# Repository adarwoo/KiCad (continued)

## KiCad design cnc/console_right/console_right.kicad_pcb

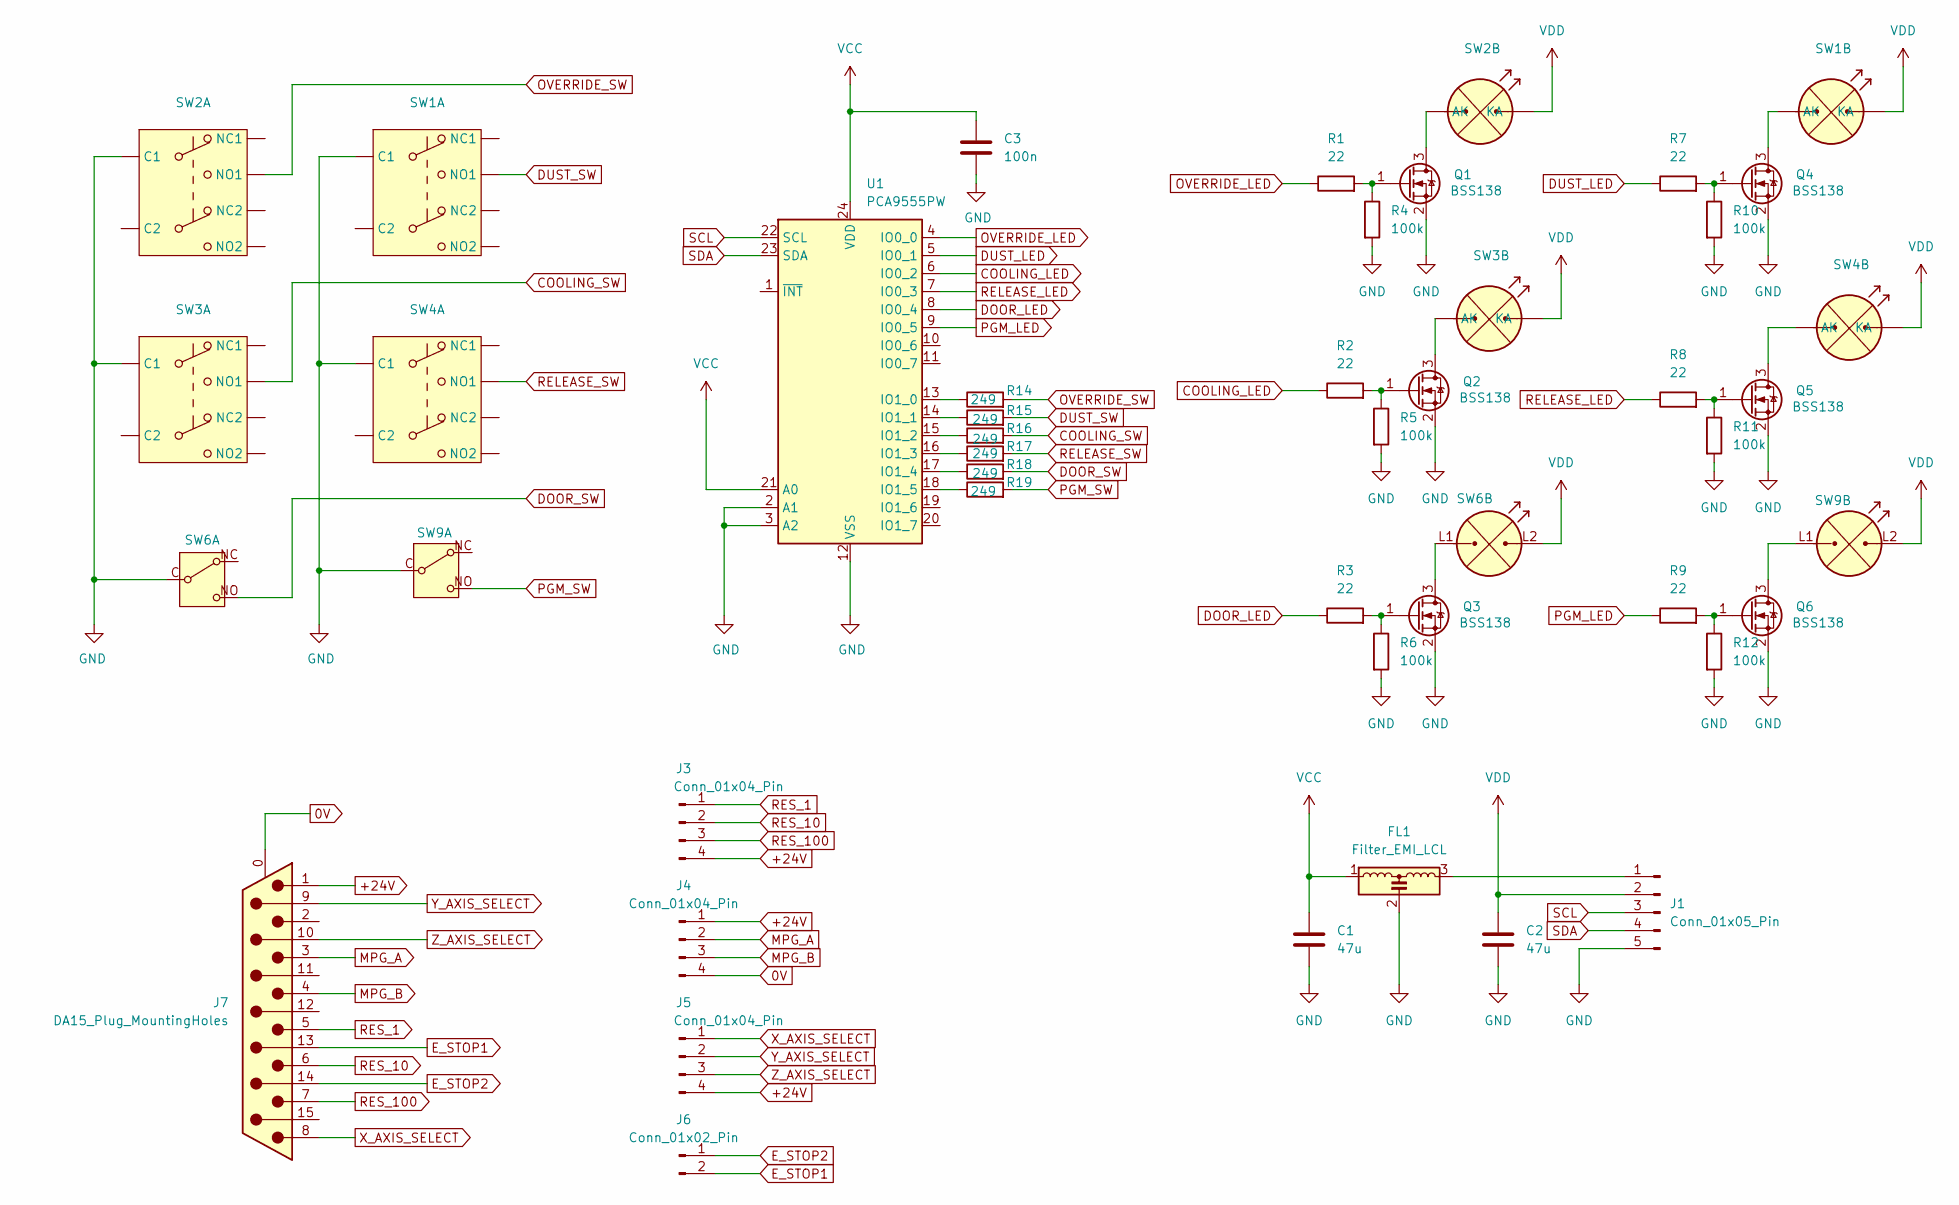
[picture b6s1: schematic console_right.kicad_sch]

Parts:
C1, C2: 47u; C_1210_3225Metric_Pad1.33x2.70mm_HandSolder
C3: 100n; C_0603_1608Metric_Pad1.08x0.95mm_HandSolder
FL1: Filter_EMI_LCL; Murata_NFM61R
J1: Conn_01x05_Pin; Molex_KK-254_AE-6410-05A_1x05_P2.54mm_Vertical
J3, J4, J5: Conn_01x04_Pin; Molex_KK-254_AE-6410-04A_1x04_P2.54mm_Vertical
J6: Conn_01x02_Pin; Molex_KK-254_AE-6410-02A_1x02_P2.54mm_Vertical
J7: DA15_Plug_MountingHoles; DSUB-15_Male_Horizontal_P2.77x2.84mm_EdgePinOffset7.70mm_Ho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
Q1, Q2, Q3, Q4, Q5, Q6: BSS138; SOT-23
R1, R2, R3, R7, R8, R9: 22; R_1206_3216Metric_Pad1.30x1.75mm_HandSolder
R4, R5, R6, R10, R11, R12: 100k; R_1206_3216Metric_Pad1.30x1.75mm_HandSolder
R14, R15, R16, R17, R18, R19: 249; R_1206_3216Metric_Pad1.30x1.75mm_HandSolder
SW1, SW2, SW3, SW4: DPDT-LED12V
SW6, SW9: PUSH_STDP_LED
U1: PCA9555PW; TSSOP-24_4.4x7.8mm_P0.65mm

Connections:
0V: J4.4, J7.0 (PAD)
+24V: J3.4, J4.1, J5.4, J7.1
COOLING_LED: R2.1, U1.6 (IO0_2)
COOLING_SW: R16.2, SW3.NO1
DOOR_LED: R3.1, U1.8 (IO0_4)
DOOR_SW: R18.2, SW6.NO
DUST_LED: R7.1, U1.5 (IO0_1)
DUST_SW: R15.2, SW1.NO1
E_STOP1: J6.2, J7.13
E_STOP2: J6.1, J7.14
GND: C1.2, C2.2, C3.2, FL1.2, J1.5, Q1.2 (S), Q2.2 (S), Q3.2 (S), Q4.2 (S), Q5.2 (S), Q6.2 (S), R4.2, R5.2, R6.2, R10.2, R11.2, R12.2, SW1.C1, SW2.C1, SW3.C1, SW4.C1, SW6.C, SW9.C, U1.2 (A1), U1.3 (A2), U1.12 (VSS)
MPG_A: J4.2, J7.3
MPG_B: J4.3, J7.4
unnamed: FL1.3, J1.1
unnamed: Q1.3 (D), SW2.L1 (AK)
unnamed: Q1.1 (G), R1.2, R4.1
unnamed: Q2.3 (D), SW3.L1 (AK)
unnamed: Q2.1 (G), R2.2, R5.1
unnamed: Q3.3 (D), SW6.L1 (AK)
unnamed: Q3.1 (G), R3.2, R6.1
unnamed: Q4.3 (D), SW1.L1 (AK)
unnamed: Q4.1 (G), R7.2, R10.1
unnamed: Q5.3 (D), SW4.L1 (AK)
unnamed: Q5.1 (G), R8.2, R11.1
unnamed: Q6.3 (D), SW9.L1 (AK)
unnamed: Q6.1 (G), R9.2, R12.1
unnamed: R14.1, U1.13 (IO1_0)
unnamed: R15.1, U1.14 (IO1_1)
unnamed: R16.1, U1.15 (IO1_2)
unnamed: R17.1, U1.16 (IO1_3)
unnamed: R18.1, U1.17 (IO1_4)
unnamed: R19.1, U1.18 (IO1_5)
OVERRIDE_LED: R1.1, U1.4 (IO0_0)
OVERRIDE_SW: R14.2, SW2.NO1
PGM_LED: R9.1, U1.9 (IO0_5)
PGM_SW: R19.2, SW9.NO
RELEASE_LED: R8.1, U1.7 (IO0_3)
RELEASE_SW: R17.2, SW4.NO1
RES_1: J3.1, J7.5
RES_10: J3.2, J7.6
RES_100: J3.3, J7.7
SCL: J1.3, U1.22 (SCL)
SDA: J1.4, U1.23 (SDA)
VCC: C1.1, C3.1, FL1.1, U1.21 (A0), U1.24 (VDD)
VDD: C2.1, J1.2, SW1.L2 (KA), SW2.L2 (KA), SW3.L2 (KA), SW4.L2 (KA), SW6.L2 (KA), SW9.L2 (KA)
X_AXIS_SELECT: J5.1, J7.8
Y_AXIS_SELECT: J5.2, J7.9
Z_AXIS_SELECT: J5.3, J7.10

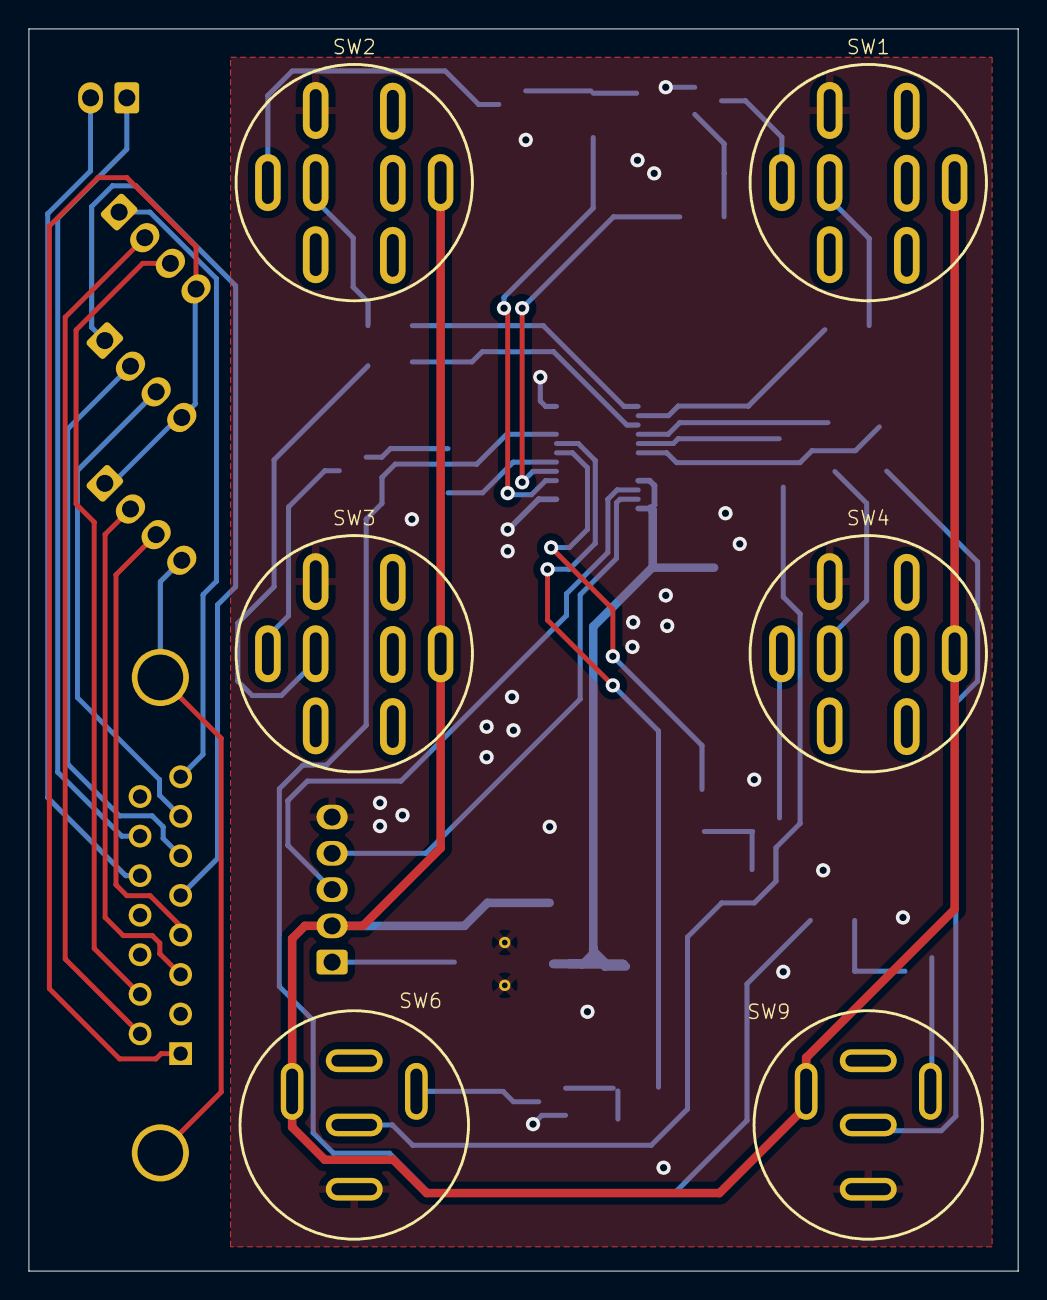
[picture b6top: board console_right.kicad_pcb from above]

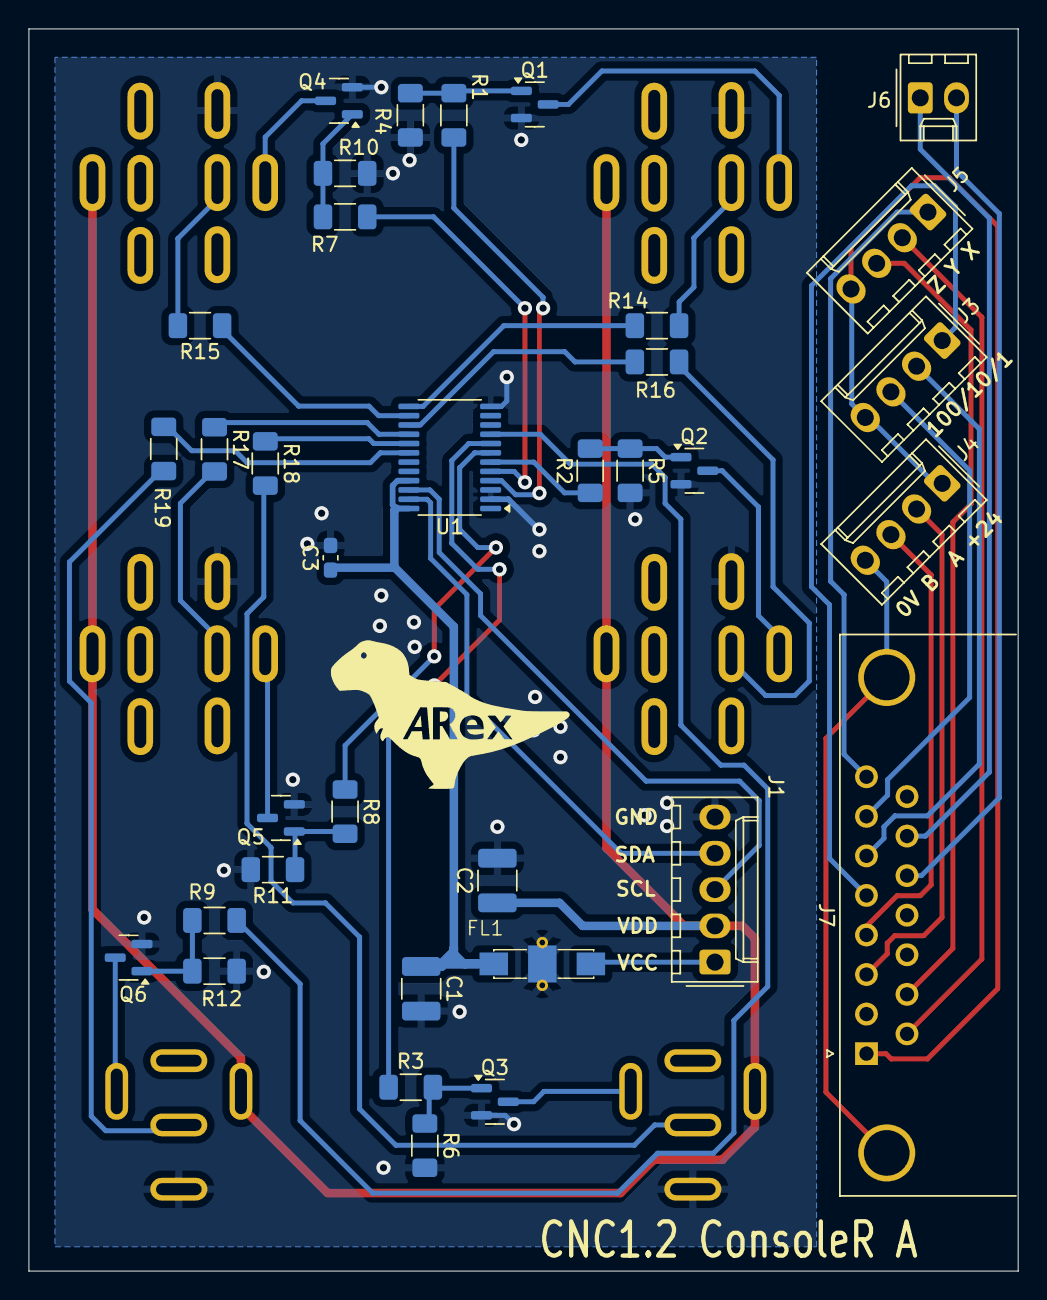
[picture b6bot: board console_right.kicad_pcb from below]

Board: 2 copper layers, 69.3 x 87.0 mm, 41 parts (35 on the bottom side), 48 nets.

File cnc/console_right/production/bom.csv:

Designator,Footprint,Quantity,Value,LCSC Part #
"C1, C2",1210,2,47u,
C3,0603,1,100n,
FL1,Murata_NFM61R,1,Filter_EMI_LCL,
J1,Molex_KK-254_AE-6410-05A_1x05_P2.54mm_Vertical,1,Conn_01x05_Pin,
"J3, J4, J5",Molex_KK-254_AE-6410-04A_1x04_P2.54mm_Vertical,3,Conn_01x04_Pin,
J6,Molex_KK-254_AE-6410-02A_1x02_P2.54mm_Vertical,1,Conn_01x02_Pin,
J7,DSUB-15_Male_Horizontal_P2.77x2.84mm_EdgePinOffset7.70mm_Housed_MountingHolesOffset9.12mm,1,DA15_Plug_MountingHoles,
"Q1, Q2, Q3, Q4, Q5, Q6",SOT-23,6,BSS138,
"R1, R2, R3, R7, R8, R9",1206,6,22,
"R10, R11, R12, R4, R5, R6",1206,6,100k,
"R14, R15, R16, R17, R18, R19",1206,6,332,
"SW1, SW2, SW3, SW4",DPDT-LED12V,4,~,
"SW6, SW9",PUSH_STDP_LED,2,~,
U1,TSSOP-24_4.4x7.8mm_P0.65mm,1,PCA9555PW,

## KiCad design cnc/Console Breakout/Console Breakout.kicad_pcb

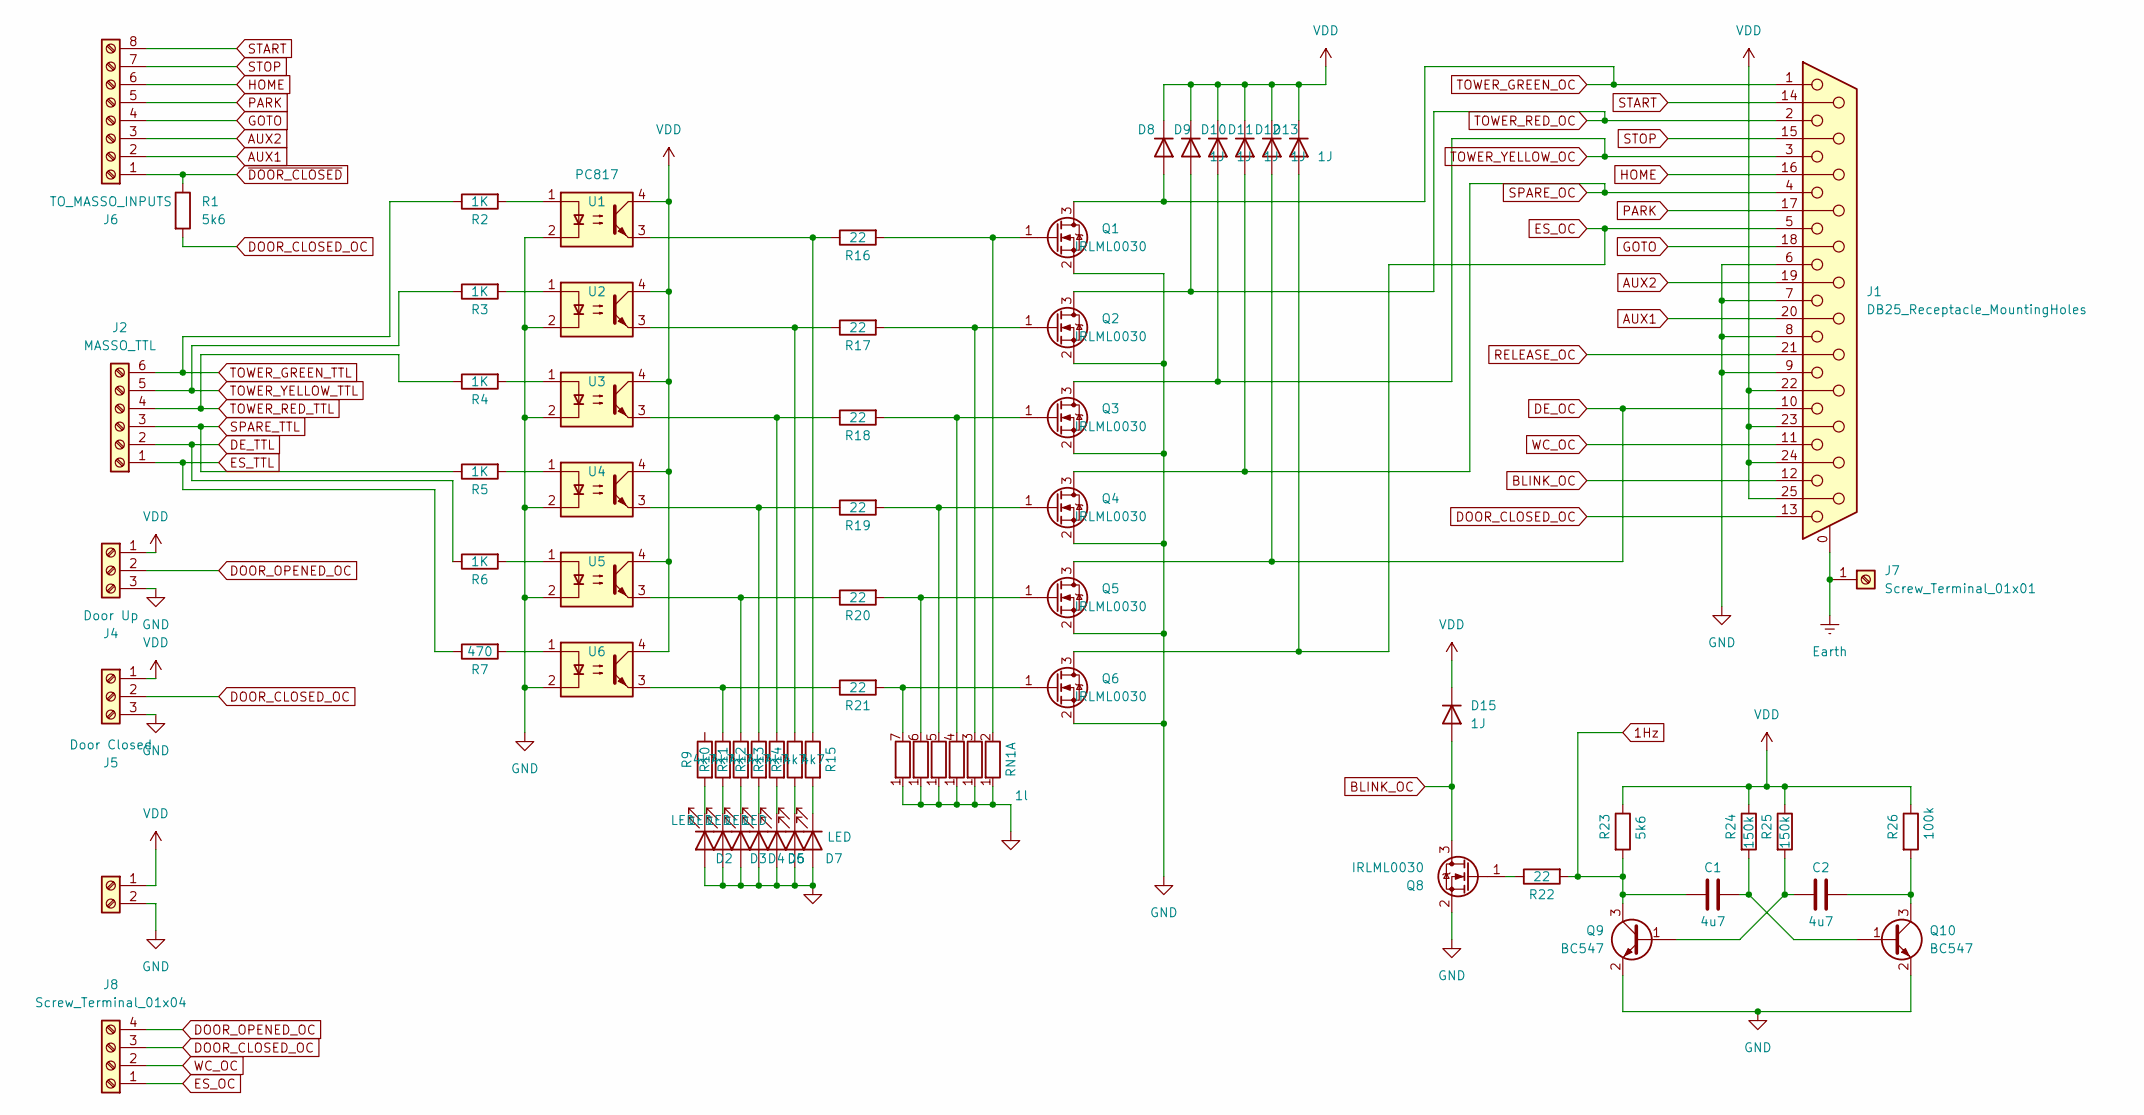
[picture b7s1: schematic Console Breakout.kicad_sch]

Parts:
C1, C2: 4u7; CP_EIA-6032-28_Kemet-C_Pad2.25x2.35mm_HandSolder
D1, D2, D3, D4, D5, D6, D7: LED; LED_D3.0mm
D8, D9, D10, D11, D12, D13: 1J; D_MicroSMP_AK
D15: 1J; D_SMA
J1: DB25_Receptacle_MountingHoles; DSUB-25_Female_Vertical_P2.77x2.84mm_MountingHoles
J2: MASSO_TTL; PhoenixContact_MCV_1,5_6-G-3.81_1x06_P3.81mm_Vertical
J3: Screw_Terminal_01x02; PhoenixContact_MCV_1,5_2-G-3.81_1x02_P3.81mm_Vertical
J4: Door Up; PhoenixContact_MCV_1,5_3-G-3.81_1x03_P3.81mm_Vertical
J5: Door Closed; PhoenixContact_MCV_1,5_3-G-3.81_1x03_P3.81mm_Vertical
J6: TO_MASSO_INPUTS; PhoenixContact_MCV_1,5_8-G-3.81_1x08_P3.81mm_Vertical
J7: Screw_Terminal_01x01; TerminalBlock_MetzConnect_360410_1x01_Horizontal_ScrewM3.0
J8: Screw_Terminal_01x04; PhoenixContact_MCV_1,5_4-G-3.81_1x04_P3.81mm_Vertical
Q1, Q2, Q3, Q4, Q5, Q6, Q8: IRLML0030; SOT-23
Q9, Q10: BC547; SOT-23
R1, R23: 5k6; R_1206_3216Metric_Pad1.30x1.75mm_HandSolder
R2, R3, R4, R5, R6: 1K; R_1206_3216Metric_Pad1.30x1.75mm_HandSolder
R7: 470; R_1206_3216Metric_Pad1.30x1.75mm_HandSolder
R9, R10, R11, R12, R13, R14, R15: 4k7; R_1206_3216Metric_Pad1.30x1.75mm_HandSolder
R16, R17, R18, R19, R20, R21, R22: 22; R_1206_3216Metric_Pad1.30x1.75mm_HandSolder
R24, R25: 150k; R_1206_3216Metric_Pad1.30x1.75mm_HandSolder
R26: 100k; R_1206_3216Metric_Pad1.30x1.75mm_HandSolder
RN1: 1l; R_Array_SIP8
U1, U2, U3, U4, U5, U6: PC817; DIP-4_W7.62mm

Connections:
1Hz: C1.1, Q9.3 (C), R22.2, R23.2
AUX1: J1.20, J6.2
AUX2: J1.19, J6.3
BLINK_OC: D15.2 (A), J1.12, Q8.3 (D)
DE_OC: D12.2 (A), J1.10, Q5.3 (D)
DE_TTL: J2.2, R6.1
DOOR_CLOSED_OC: J1.13, J5.2, J8.3, R1.2
DOOR_OPENED_OC: J4.2, J8.4
ES_OC: D13.2 (A), J1.5, J8.1, Q6.3 (D)
ES_TTL: J2.1, R7.1
Earth: J1.0 (PAD), J7.1
GND: D1.2 (A), D2.2 (A), D3.2 (A), D4.2 (A), D5.2 (A), D6.2 (A), D7.2 (A), J1.6, J1.7, J1.8, J1.9, J3.2, J4.3, J5.3, Q1.2 (S), Q2.2 (S), Q3.2 (S), Q4.2 (S), Q5.2 (S), Q6.2 (S), Q8.2 (S), Q9.2 (E), Q10.2 (E), RN1.1 (R1), U1.2, U2.2, U3.2, U4.2, U5.2, U6.2
GOTO: J1.18, J6.4
HOME: J1.16, J6.6
unnamed: D1.1 (K), R9.2
unnamed: D2.1 (K), R10.2
unnamed: D3.1 (K), R11.2
unnamed: D4.1 (K), R12.2
unnamed: D5.1 (K), R13.2
unnamed: D6.1 (K), R14.2
unnamed: D7.1 (K), R15.2
unnamed: Q1.1 (G), R16.2, RN1.2 (R1.2)
unnamed: Q2.1 (G), R17.2, RN1.3 (R2.2)
unnamed: Q3.1 (G), R18.2, RN1.4 (R3.2)
unnamed: Q4.1 (G), R19.2, RN1.5 (R4.2)
unnamed: Q5.1 (G), R20.2, RN1.6 (R5.2)
unnamed: Q6.1 (G), R21.2, RN1.7 (R6.2)
unnamed: Q8.1 (G), R22.1
unnamed: C2.1, Q9.1 (B), R25.2
unnamed: C1.2, Q10.1 (B), R24.2
unnamed: C2.2, Q10.3 (C), R26.2
unnamed: R2.2, U1.1
unnamed: R3.2, U2.1
unnamed: R4.2, U3.1
unnamed: R5.2, U4.1
unnamed: R6.2, U5.1
unnamed: R7.2, U6.1
unnamed: R10.1, R21.1, U6.3
unnamed: R11.1, R20.1, U5.3
unnamed: R12.1, R19.1, U4.3
unnamed: R13.1, R18.1, U3.3
unnamed: R14.1, R17.1, U2.3
unnamed: R15.1, R16.1, U1.3
PARK: J1.17, J6.5
RELEASE_OC: J1.21
SPARE_OC: D11.2 (A), J1.4, Q4.3 (D)
SPARE_TTL: J2.3, R5.1
START: J1.14, J6.8
STOP: J1.15, J6.7
TOWER_GREEN_OC: D8.2 (A), J1.1, Q1.3 (D)
TOWER_GREEN_TTL: J2.6, R2.1
TOWER_RED_OC: D9.2 (A), J1.2, Q2.3 (D)
TOWER_RED_TTL: J2.4, R4.1
TOWER_YELLOW_OC: D10.2 (A), J1.3, Q3.3 (D)
TOWER_YELLOW_TTL: J2.5, R3.1
VDD: D8.1 (K), D9.1 (K), D10.1 (K), D11.1 (K), D12.1 (K), D13.1 (K), D15.1 (K), J1.22, J1.23, J1.24, J1.25, J3.1, J4.1, J5.1, R23.1, R24.1, R25.1, R26.1, U1.4, U2.4, U3.4, U4.4, U5.4, U6.4
WC_OC: J1.11, J8.2
~DOOR_CLOSED: J6.1, R1.1

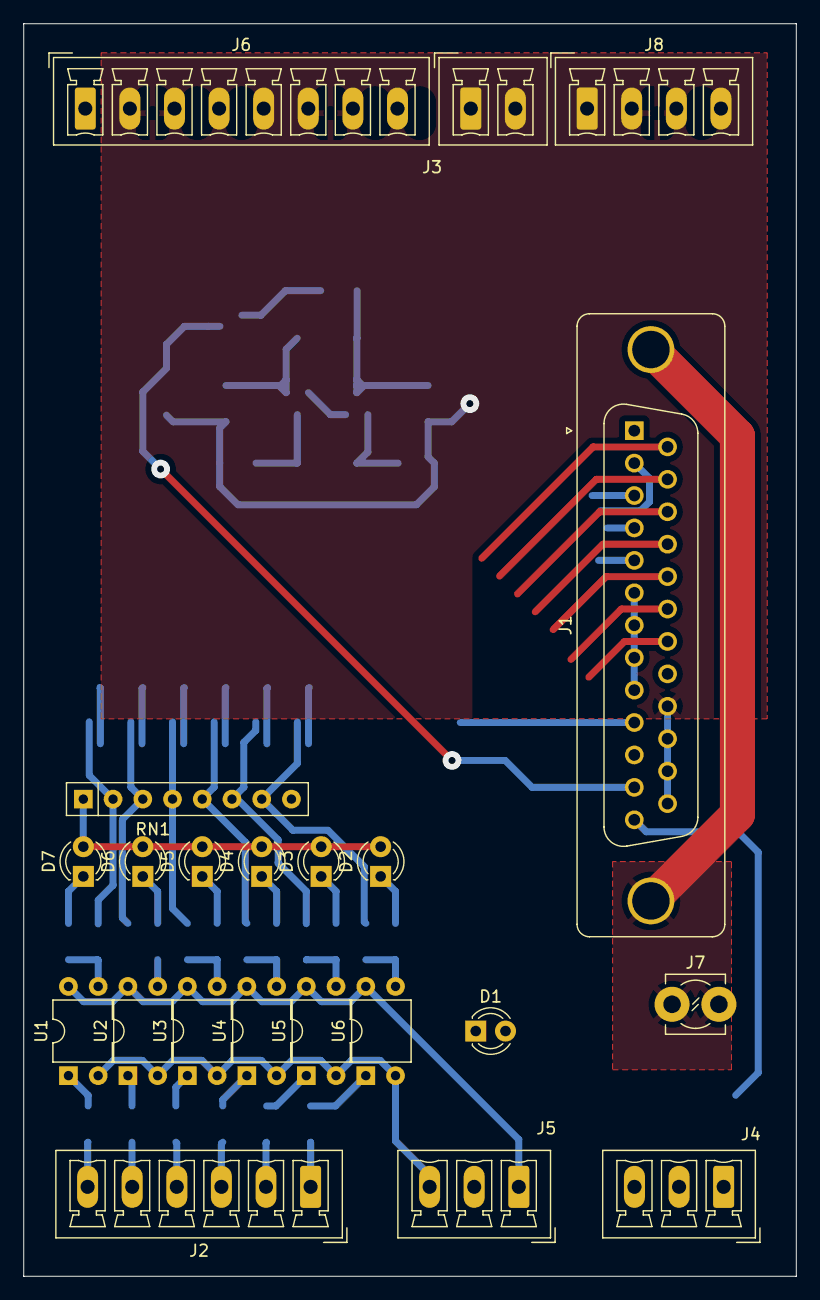
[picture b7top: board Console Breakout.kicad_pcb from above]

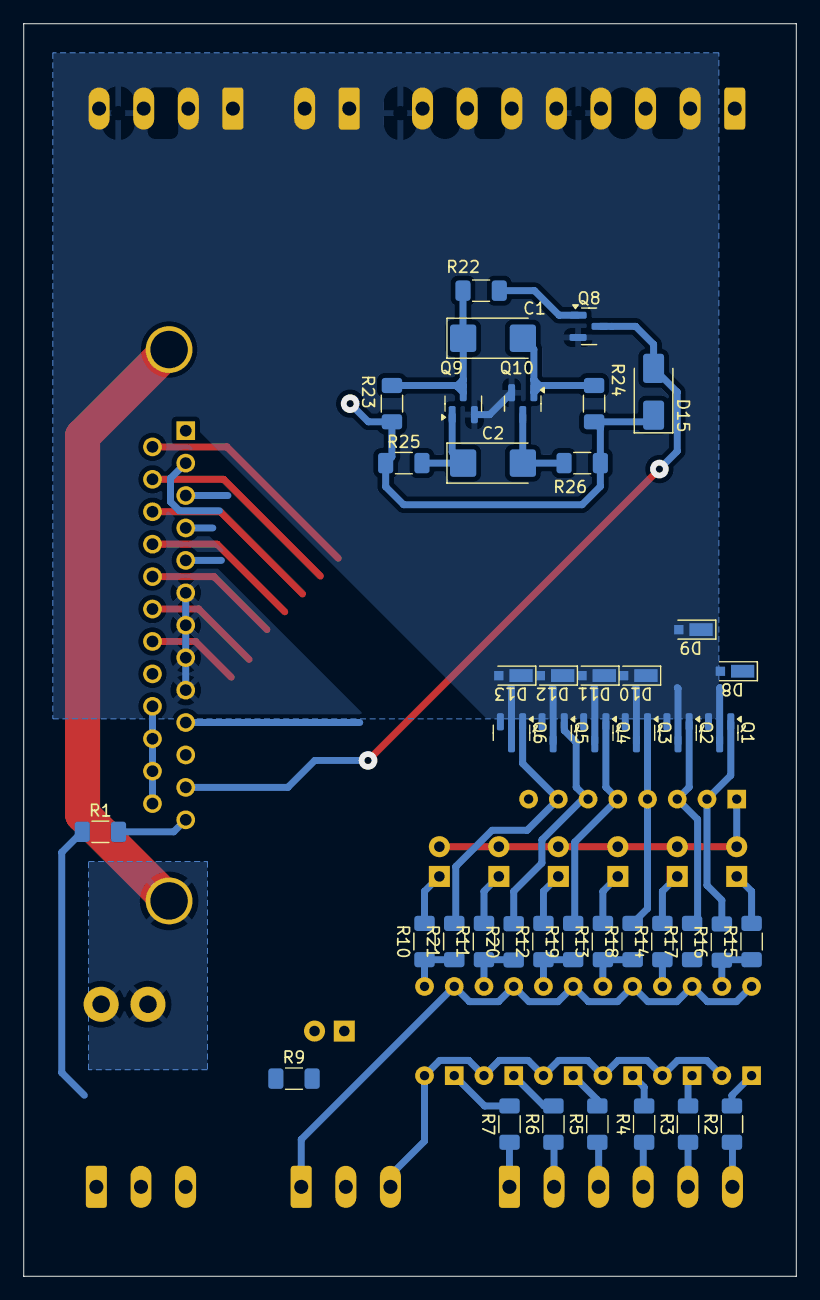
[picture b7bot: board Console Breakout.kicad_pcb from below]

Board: 2 copper layers, 66.0 x 107.0 mm, 65 parts (43 on the bottom side), 57 nets.

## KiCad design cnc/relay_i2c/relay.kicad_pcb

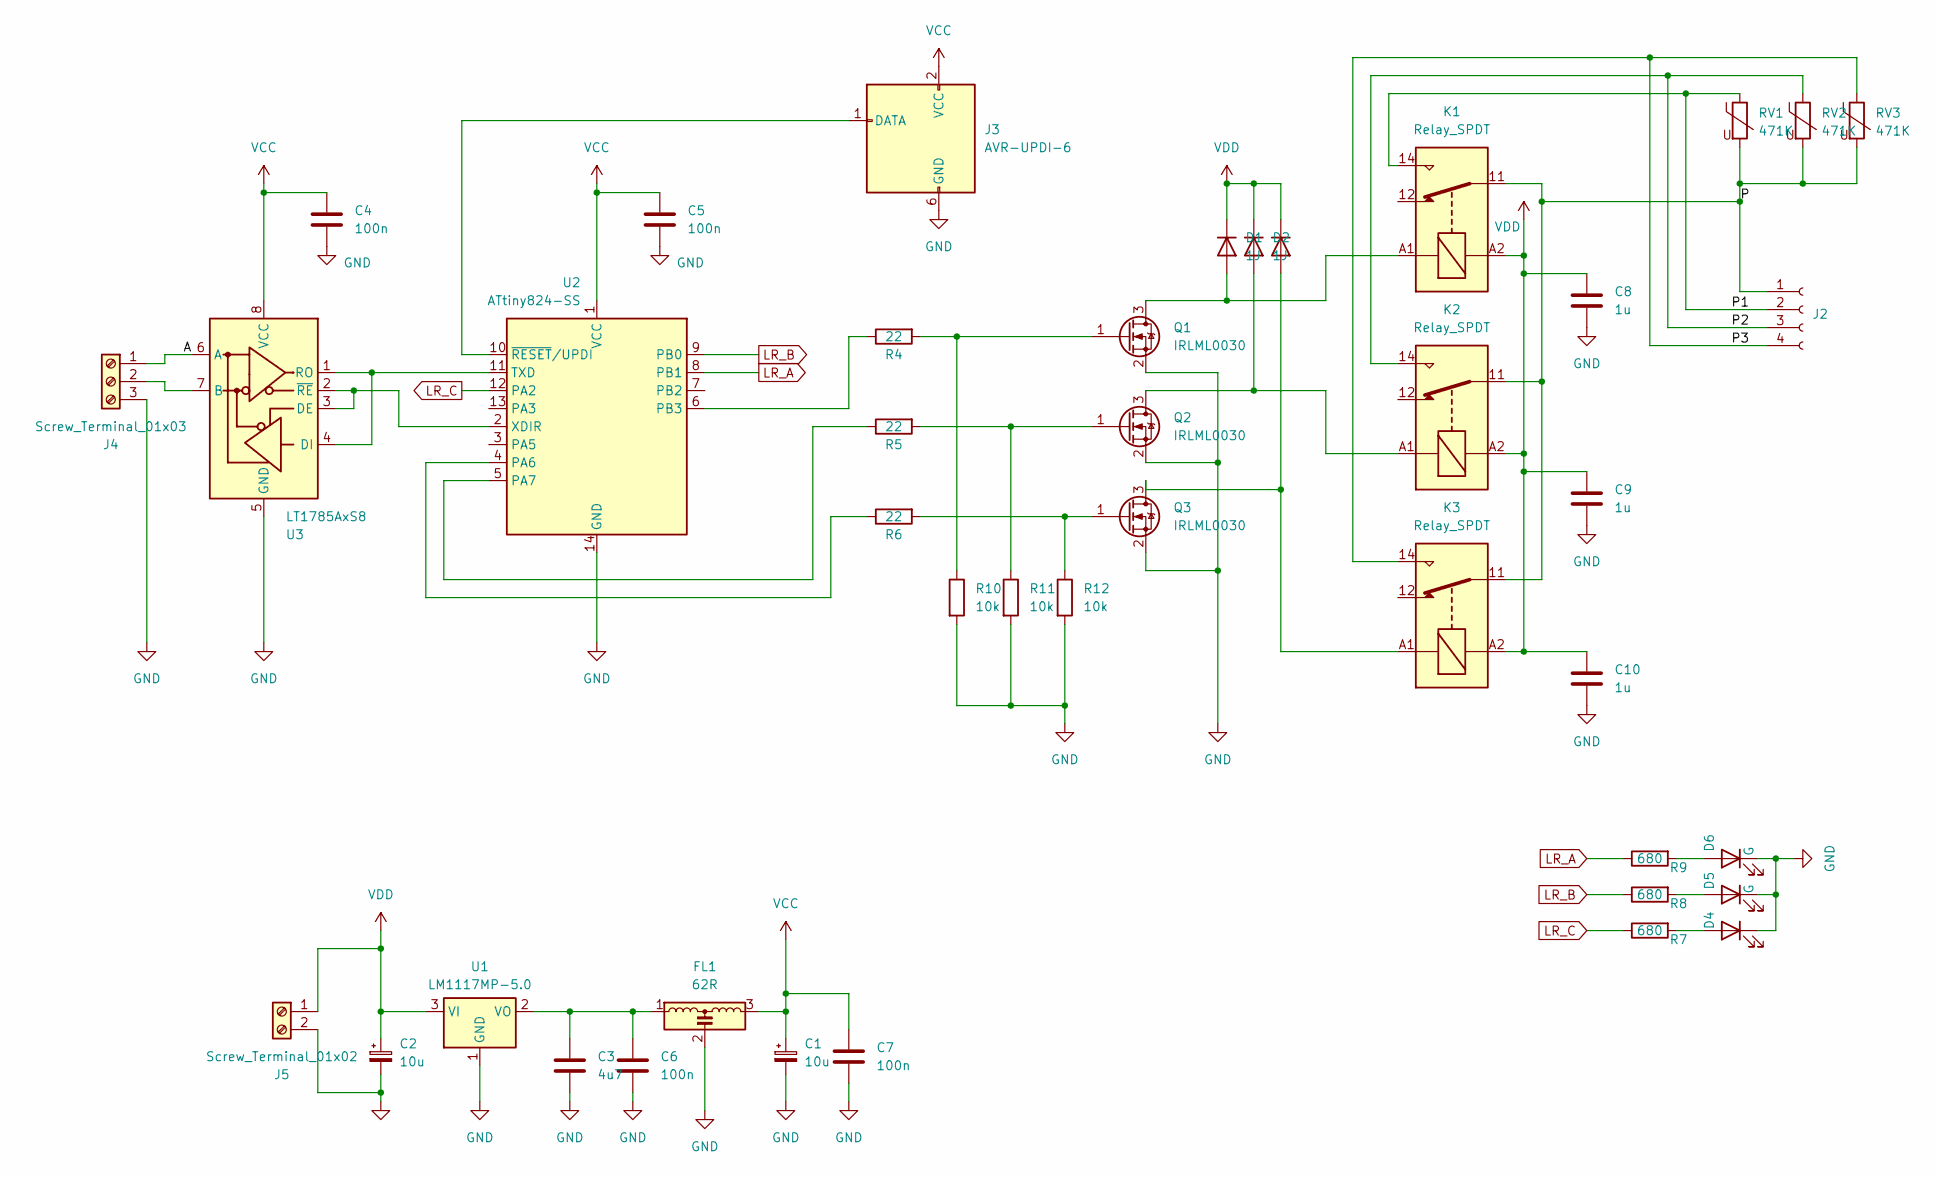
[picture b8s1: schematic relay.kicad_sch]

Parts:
C1, C2: 10u; CP_EIA-6032-28_Kemet-C
C3: 4u7; C_1206_3216Metric_Pad1.33x1.80mm_HandSolder
C4, C5, C6, C7: 100n; C_0805_2012Metric_Pad1.18x1.45mm_HandSolder
C8, C9, C10: 1u; C_1206_3216Metric_Pad1.33x1.80mm_HandSolder
D1, D2, D3: 1J; D_SMA
D4, D5, D6: G; LED_D3.0mm
FL1: 62R; Murata_NFM61R
J2: TerminalBlock_Phoenix_MKDS-1,5-4_1x04_P5.00mm_Horizontal
J3: AVR-UPDI-6; PinHeader_2x03_P2.54mm_Vertical
J4: Screw_Terminal_01x03; PhoenixContact_MCV_1,5_3-G-3.81_1x03_P3.81mm_Vertical
J5: Screw_Terminal_01x02; PhoenixContact_MCV_1,5_2-G-3.81_1x02_P3.81mm_Vertical
K1, K2, K3: Relay_SPDT; Relay_SPDT_Omron_G2RL-1-E
Q1, Q2, Q3: IRLML0030; SOT-23
R4, R5, R6: 22; R_1206_3216Metric_Pad1.30x1.75mm_HandSolder
R7, R8, R9: 680; R_1206_3216Metric_Pad1.30x1.75mm_HandSolder
R10, R11, R12: 10k; R_1206_3216Metric_Pad1.30x1.75mm_HandSolder
RV1, RV2, RV3: 471K; RV_Disc_D9mm_W3.3mm_P5mm
U1: LM1117MP-5.0; SOT-223-3_TabPin2
U2: ATtiny824-SS; SOIC-14_3.9x8.7mm_P1.27mm
U3: LT1785AxS8; SOIC-8_3.9x4.9mm_P1.27mm

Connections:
/A: J4.1, U3.6 (A)
/P: J2.1, K1.11, K2.11, K3.11, RV1.2, RV2.2, RV3.2
/P1: J2.2, K1.14, RV1.1
/P2: J2.3, K2.14, RV2.1
/P3: J2.4, K3.14, RV3.1
GND: C1.2, C2.2, C3.2, C4.2, C5.2, C6.2, C7.2, C8.2, C9.2, C10.2, D4.1 (K), D5.1 (K), D6.1 (K), FL1.2, J3.6 (GND), J4.3, J5.2, Q1.2 (S), Q2.2 (S), Q3.2 (S), R10.2, R11.2, R12.2, U1.1 (GND), U2.14 (GND), U3.5 (GND)
LR_A: R9.1, U2.8 (PB1)
LR_B: R8.1, U2.9 (PB0)
LR_C: R7.1, U2.12 (PA2)
unnamed: D1.2 (A), K1.A1, Q1.3 (D)
unnamed: D2.2 (A), K2.A1, Q2.3 (D)
unnamed: D3.2 (A), K3.A1, Q3.3 (D)
unnamed: D4.2 (A), R7.2
unnamed: D5.2 (A), R8.2
unnamed: D6.2 (A), R9.2
unnamed: J3.1 (DATA), U2.10 (~RESET/UPDI)
unnamed: J4.2, U3.7 (B)
unnamed: Q1.1 (G), R4.2, R10.1
unnamed: Q2.1 (G), R5.2, R11.1
unnamed: Q3.1 (G), R6.2, R12.1
unnamed: C3.1, C6.1, FL1.1, U1.2 (VO)
unnamed: U2.11 (TXD), U3.1 (RO), U3.4 (DI)
unnamed: U2.2 (XDIR), U3.2 (~RE), U3.3 (DE)
unnamed: R6.1, U2.4 (PA6)
unnamed: R5.1, U2.5 (PA7)
unnamed: R4.1, U2.6 (PB3)
VCC: C1.1, C4.1, C5.1, C7.1, FL1.3, J3.2 (VCC), U2.1 (VCC), U3.8 (VCC)
VDD: C2.1, C8.1, C9.1, C10.1, D1.1 (K), D2.1 (K), D3.1 (K), J5.1, K1.A2, K2.A2, K3.A2, U1.3 (VI)

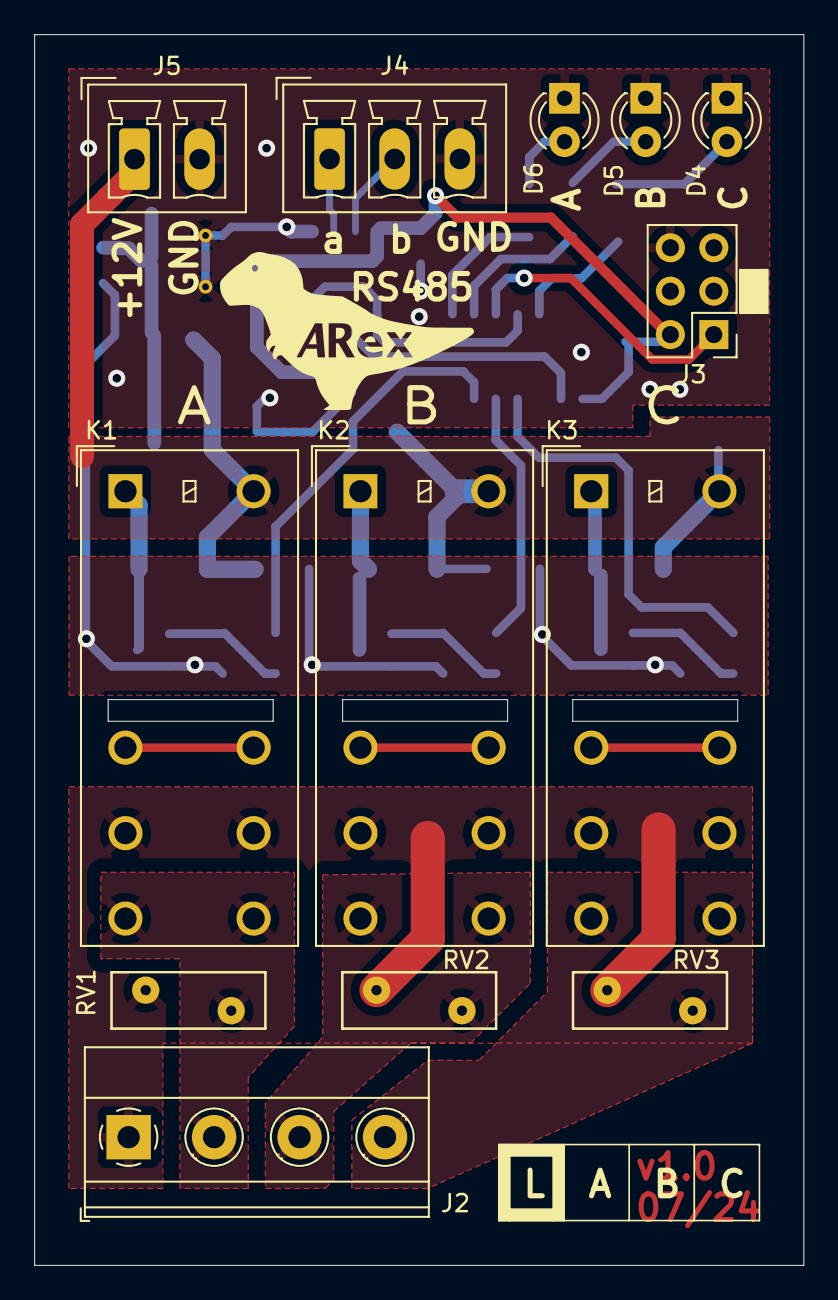
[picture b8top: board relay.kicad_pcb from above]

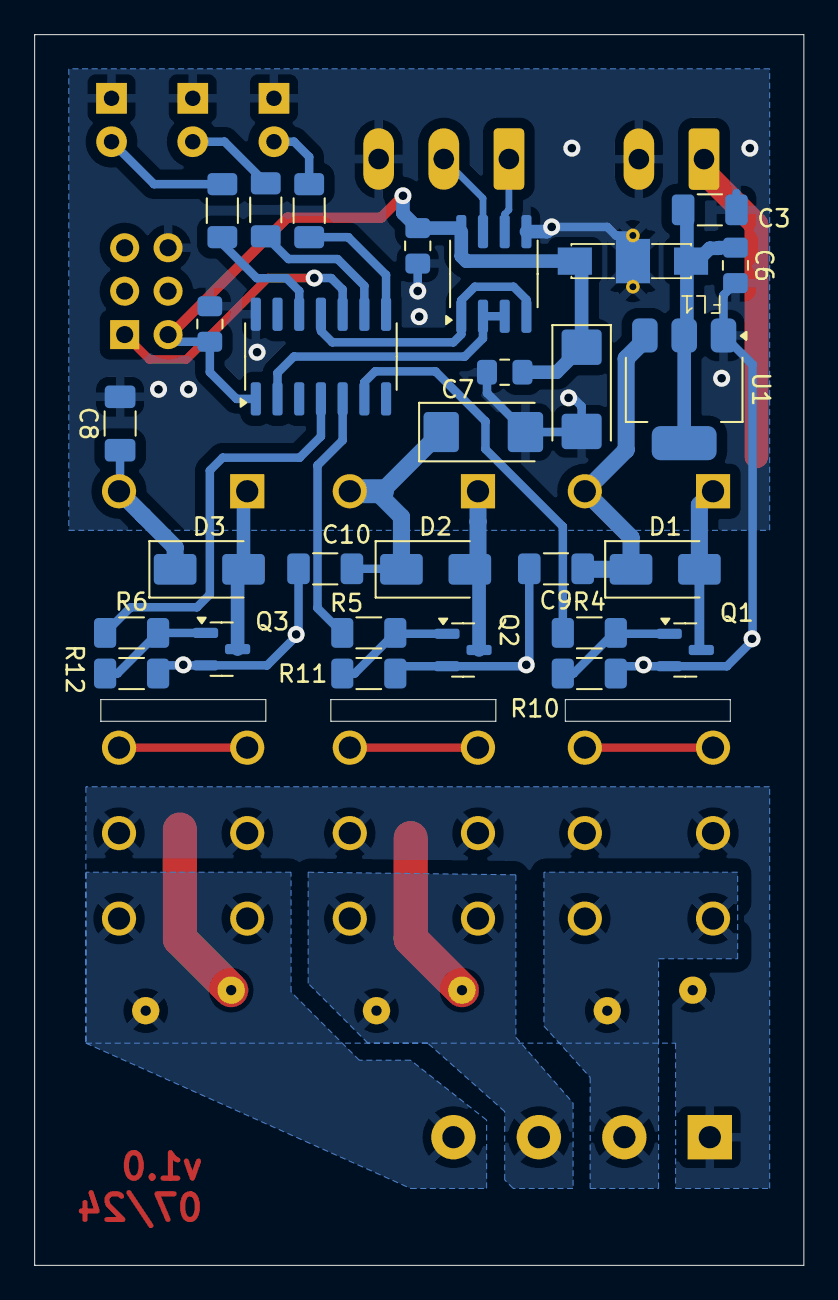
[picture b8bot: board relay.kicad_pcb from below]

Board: 2 copper layers, 45.0 x 72.0 mm, 42 parts (29 on the bottom side), 28 nets.

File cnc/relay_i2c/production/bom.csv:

Designator,Footprint,Quantity,Value,LCSC Part #
"C1, C2",CP_EIA-6032-28_Kemet-C,2,10u,
"C10, C8, C9",1206,3,1u,
C3,1206,1,4u7,
"C4, C5, C6, C7",0805,4,100n,
"D1, D2, D3",D_SMA,3,1J,
"D4, D5, D6",LED_D3.0mm,3,G,
FL1,Murata_NFM61R,1,62R,
J2,"TerminalBlock_Phoenix_MKDS-1,5-4_1x04_P5.00mm_Horizontal",1,~,
J3,PinHeader_2x03_P2.54mm_Vertical,1,AVR-UPDI-6,
J4,"PhoenixContact_MCV_1,5_3-G-3.81_1x03_P3.81mm_Vertical",1,Screw_Terminal_01x03,
J5,"PhoenixContact_MCV_1,5_2-G-3.81_1x02_P3.81mm_Vertical",1,Screw_Terminal_01x02,
"K1, K2, K3",Relay_SPDT_Omron_G2RL-1-E,3,Relay_SPDT,
"Q1, Q2, Q3",SOT-23,3,IRLML0030,
"R10, R11, R12",1206,3,10k,
"R4, R5, R6",1206,3,22,
"R7, R8, R9",1206,3,680,
"RV1, RV2, RV3",RV_Disc_D9mm_W3.3mm_P5mm,3,471K,
U1,SOT-223-3_TabPin2,1,LM1117MP-5.0,
U2,SOIC-14_3.9x8.7mm_P1.27mm,1,ATtiny824-SS,
U3,SOIC-8_3.9x4.9mm_P1.27mm,1,LT1785AxS8,

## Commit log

2023-08-02 Update README.md
    Initial quick description
2023-08-02 Initial
2023-08-06 Added the python code to create the gcode from a PCB
2023-08-07 Renamed and created vscode project
2023-08-07 Created a uniontool data file to create lookup from
2023-08-07 A few renames
2023-08-07 Git ignore in place
2023-08-08 Using uniontool data
2023-08-08 Typos and reord
2023-08-08 Added yaml persistance for the rack
2023-08-09 Rack is now doing most of the work
2023-08-09 Added the asset to manage holes and contours outside of the machinig file
2023-08-11 Moved into another rePO
2024-07-18 Symbols created
2025-02-07 Everything
2025-02-23 Split sheets
2025-03-06 On-going
2025-03-06 From scratch
2025-03-07 Added 4 layers
2025-03-07 Diff pair in place
2025-03-10 Sent to production
2025-03-11 Added odg for face plate
